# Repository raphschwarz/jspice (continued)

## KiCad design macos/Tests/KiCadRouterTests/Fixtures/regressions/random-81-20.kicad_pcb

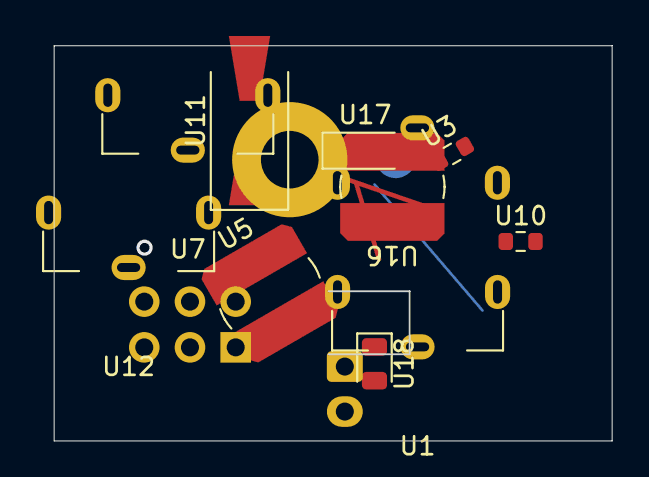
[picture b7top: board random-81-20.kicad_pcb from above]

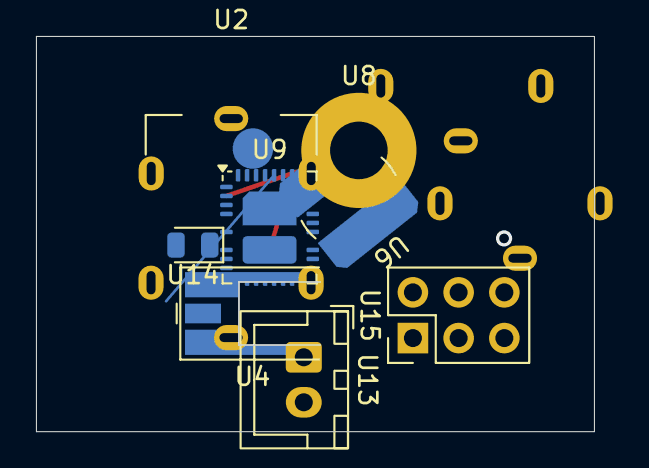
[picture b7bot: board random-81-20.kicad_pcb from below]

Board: 4 copper layers, 31.0 x 22.0 mm, 18 parts (8 on the bottom side), 6 nets.

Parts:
U1, U2, U7, U12: BatteryHolder_Keystone_590
U3, U10: R_0603_1608Metric
U4: MMCX_Molex_73415-0961_Horizontal_0.8mm-PCB
U5, U6, U16: L_Bourns_SDR0604
U8: MountingHole_3.2mm_M3_Pad
U9: Analog_QFN-28-36-2EP_5x6mm_P0.5mm
U11: D_SMA-SMB_Universal_Handsoldering
U13: JST_XH_B2B-XH-A_1x02_P2.50mm_Vertical
U14, U18: LED_0805_2012Metric
U15: PinHeader_2x03_P2.54mm_Vertical
U17: D_SOD-123

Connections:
/net3: U9.9, U9.13, U9.14, U9.20, U9.21, U12.1, U15.2, U16.2
/sub/clk: U1.1, U2.1, U4.2, U5.1, U7.1, U9.1, U9.4, U9.32, U10.1, U18.1, U18.2
GND: U7.1, U8.1, U9.6, U9.23, U9.31, U9.33, U13.1
SIG1: U1.1, U3.2, U5.2, U9.8, U9.24, U9.37, U9.38, U14.2
SIG2: U1.1, U3.1, U4.2, U7.1, U9.16, U9.25, U9.28, U9.35, U10.2, U12.1, U13.2, U15.4, U15.6, U17.2
VCC: U6.1, U6.2, U9.2, U9.3, U9.10, U9.15, U9.17, U11.1, U14.1, U15.5, U17.1

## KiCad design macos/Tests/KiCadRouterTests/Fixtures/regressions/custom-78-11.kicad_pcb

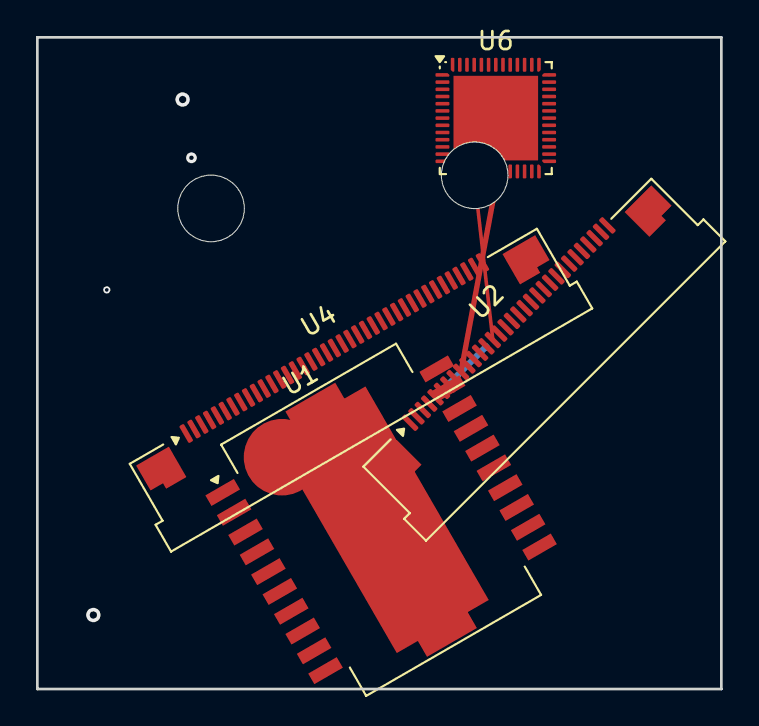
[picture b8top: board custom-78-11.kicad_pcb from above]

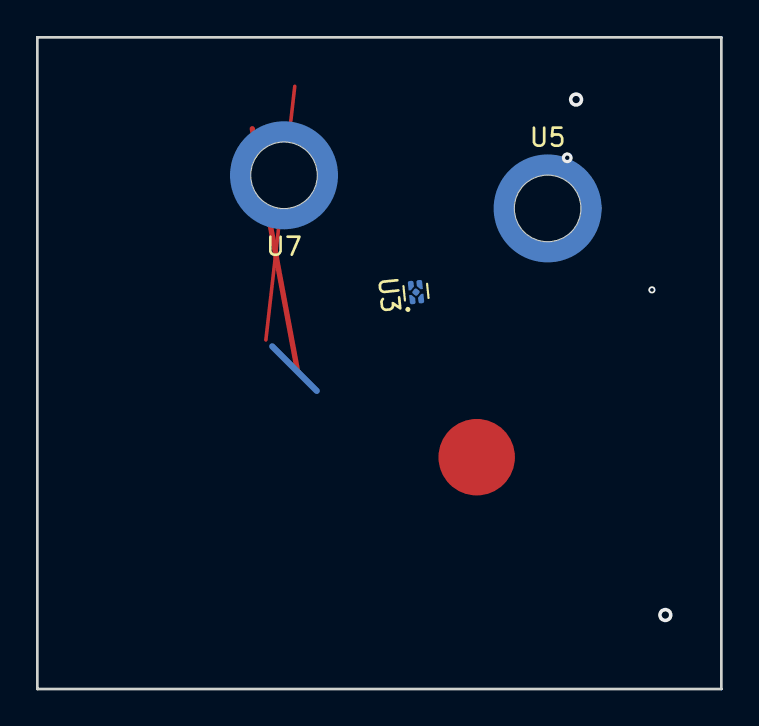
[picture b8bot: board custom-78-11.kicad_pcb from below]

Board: 4 copper layers, 38.0 x 36.2 mm, 7 parts (3 on the bottom side), 12 nets.

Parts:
U1: Infineon_PG-DSO-20-85
U2: Amphenol_F32Q-1A7x1-11032_1x32-1MP_P0.5mm_Horizon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; Amphenol_F32Q-1A7x1-11032_1x32-1MP_P0.5mm_Horizontal
U3: Texas_X2SON-5_0.8x0.8mm_P0.48mm
U4: Amphenol_F32Q-1A7x1-11039_1x39-1MP_P0.5mm_Horizon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; Amphenol_F32Q-1A7x1-11039_1x39-1MP_P0.5mm_Horizontal
U5: Mounting_Wuerth_WA-SMSI-M2.5_H6.5mm_9774065151
U6: VQFN-52-1EP_6x6mm_P0.4mm_EP4.7x4.7mm
U7: Mounting_Wuerth_WA-SMSI-M2.5_H6mm_9774060151

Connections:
/net3: U1.16, U2.1, U2.19, U3.3, U4.27, U4.33, U6.8, U6.41, U6.43
/sub/clk: U2.7, U2.13, U2.27, U2.31, U3.2, U4.19, U4.MP, U5.1, U6.19, U6.21, U6.39
D7: U1.18, U1.21, U2.16, U2.30, U4.6, U4.7, U6.9, U6.25
D12: U1.4, U1.19, U2.4, U2.10, U4.8, U4.16, U4.32, U6.2, U6.13, U6.26, U6.29
GND: U2.5, U2.15, U4.3, U4.10, U4.35, U6.7, U6.52
N2: U1.20, U2.11, U2.20, U2.23, U4.12, U4.23, U4.25, U4.26, U6.4, U6.11, U6.14, U6.15, U6.22, U6.38
N3: U1.12, U1.15, U2.9, U3.5, U4.2, U4.4, U4.15, U4.18, U4.37, U6.1, U6.27, U6.28, U6.40, U6.53
PWR1: U1.1, U1.6, U1.11, U1.13, U2.18, U2.MP, U4.5, U4.30, U6.12, U6.47, U7.1
PWR_5V: U2.6, U2.22, U2.MP, U6.3, U6.17
SIG1: U1.3, U1.5, U1.8, U1.14, U2.32, U4.20, U4.31, U5.1, U6.6, U6.10, U6.30, U6.49
SIG2: U1.7, U2.3, U2.24, U2.25, U2.29, U5.1, U6.16, U6.24, U6.42, U6.46, U6.48
VCC: U1.9, U2.8, U2.17, U2.21, U3.4, U4.13, U4.36, U7.1
